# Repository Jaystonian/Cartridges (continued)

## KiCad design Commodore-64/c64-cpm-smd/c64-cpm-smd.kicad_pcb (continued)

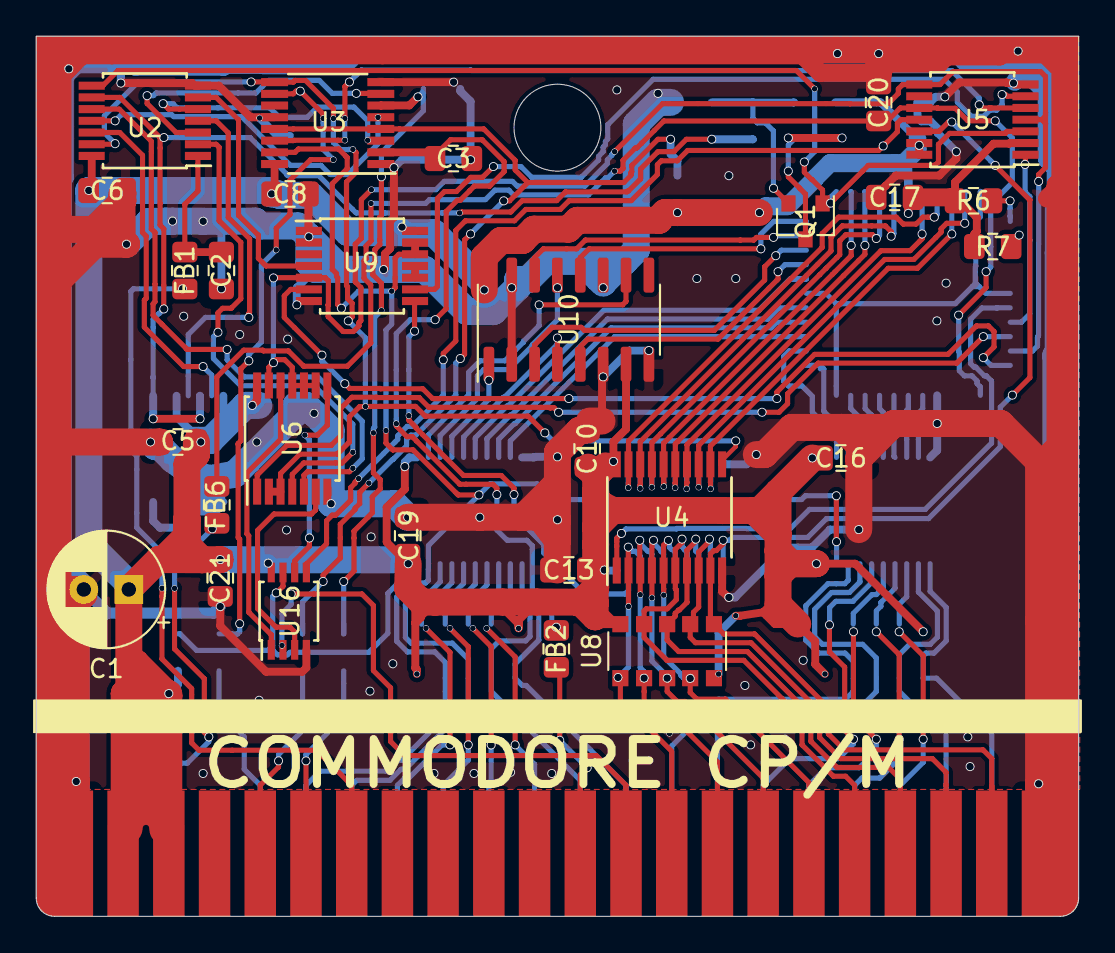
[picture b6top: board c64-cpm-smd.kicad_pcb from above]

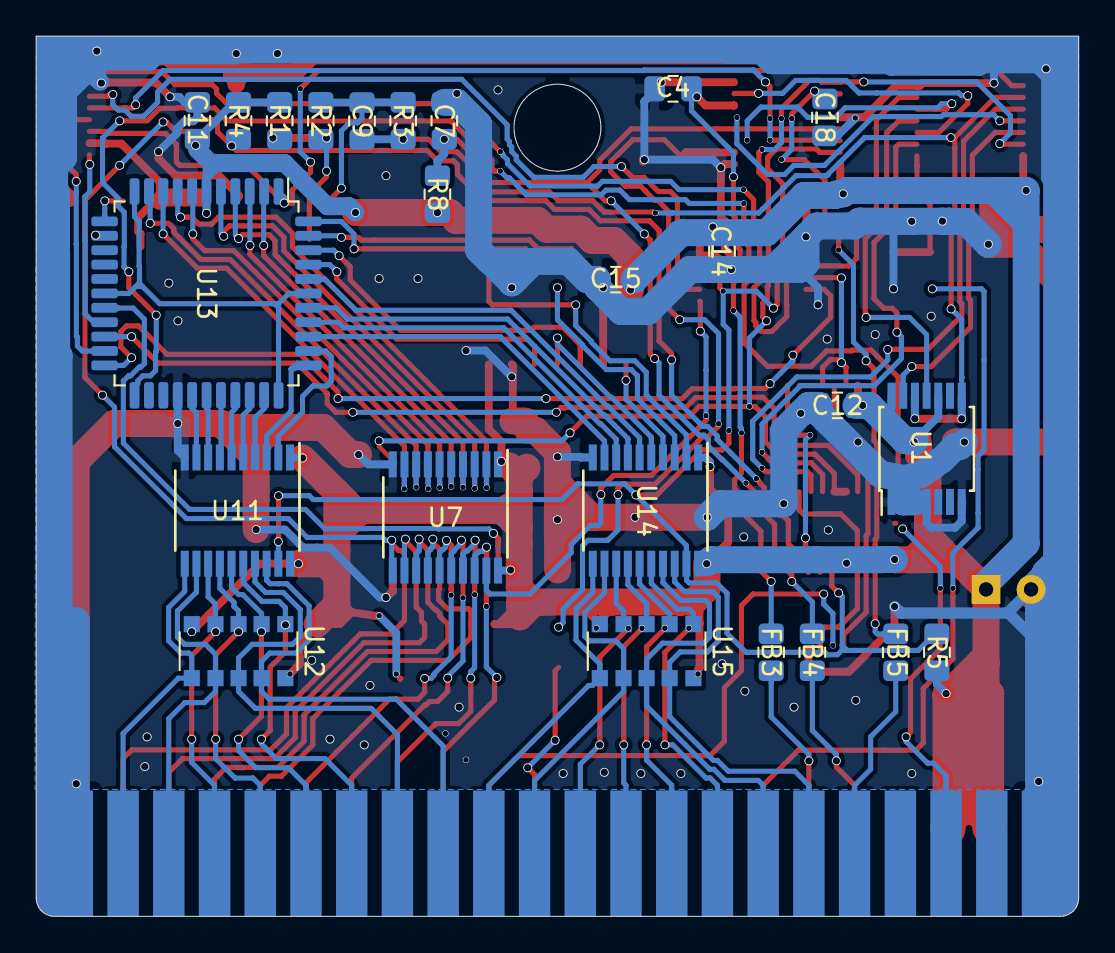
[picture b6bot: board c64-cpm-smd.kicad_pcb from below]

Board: 2 copper layers, 57.9 x 48.9 mm, 53 parts (24 on the bottom side), 97 nets.

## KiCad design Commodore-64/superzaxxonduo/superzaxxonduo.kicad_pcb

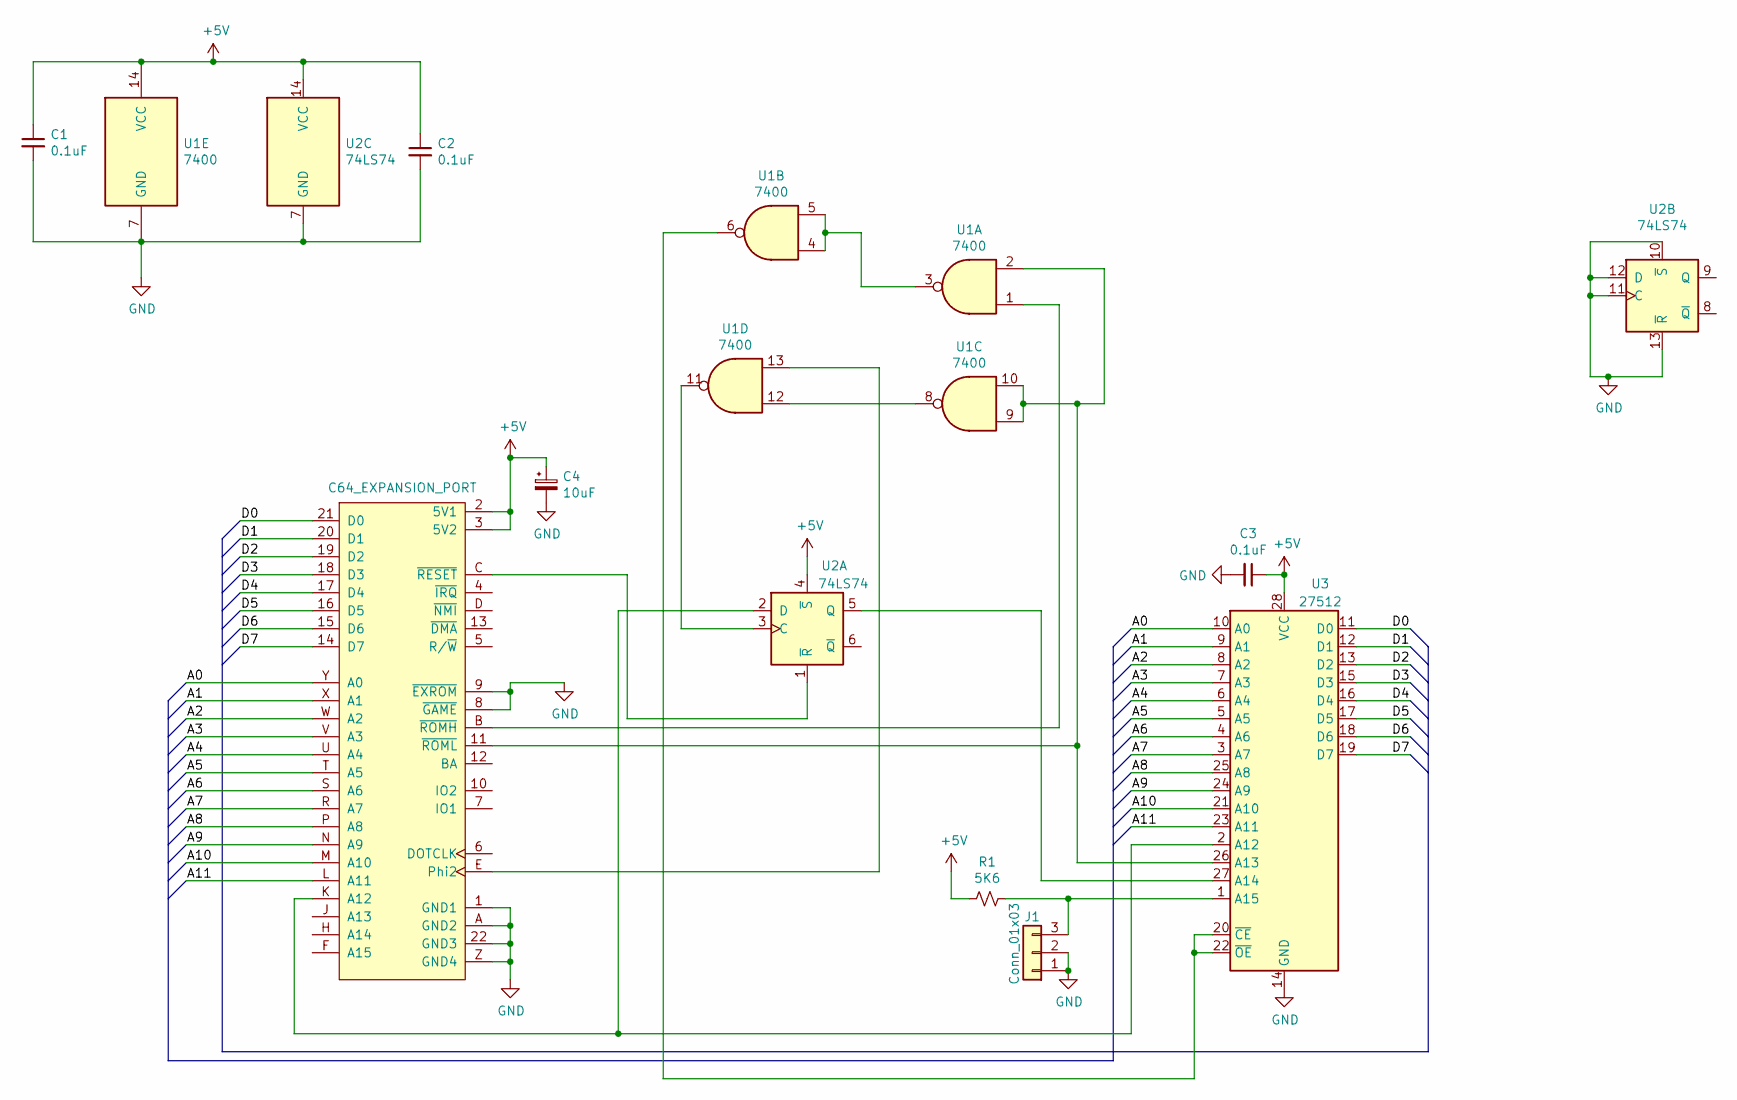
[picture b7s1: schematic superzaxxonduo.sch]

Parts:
C1, C2, C3: 0.1uF; C_Disc_D3.0mm_W1.6mm_P2.50mm
C4: 10uF; CP_Radial_D5.0mm_P2.50mm
J1: Conn_01x03; PinSocket_1x03_P2.54mm_Horizontal
R1: 5K6; R_Axial_DIN0204_L3.6mm_D1.6mm_P5.08mm_Horizontal
U1: 7400; DIP-14_W7.62mm
U2: 74LS74; DIP-14_W7.62mm
U3: 27512; DIP-28_W15.24mm
X1: C64_EXPANSION_PORT; C64_EXPANSION_CARD_49mm

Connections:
+5V: C1.1, C2.1, C3.1, C4.1, R1.1, U1.14 (VCC), U2.4 (~S), U2.14 (VCC), U3.28 (VCC), X1.2 (5V1), X1.3 (5V2); also elsewhere on the board
/A0: U3.10 (A0), X1.Y (A0); also elsewhere on the board
/A1: U3.9 (A1), X1.X (A1); also elsewhere on the board
/A2: U3.8 (A2), X1.W (A2); also elsewhere on the board
/A3: U3.7 (A3), X1.V (A3); also elsewhere on the board
/A4: U3.6 (A4), X1.U (A4); also elsewhere on the board
/A5: U3.5 (A5), X1.T (A5); also elsewhere on the board
/A6: U3.4 (A6), X1.S (A6); also elsewhere on the board
/A7: U3.3 (A7), X1.R (A7); also elsewhere on the board
/A8: U3.25 (A8), X1.P (A8); also elsewhere on the board
/A9: U3.24 (A9), X1.N (A9); also elsewhere on the board
/A10: U3.21 (A10), X1.M (A10); also elsewhere on the board
/A11: U3.23 (A11), X1.L (A11); also elsewhere on the board
/D0: U3.11 (D0), X1.21 (D0); also elsewhere on the board
/D1: U3.12 (D1), X1.20 (D1); also elsewhere on the board
/D2: U3.13 (D2), X1.19 (D2); also elsewhere on the board
/D3: U3.15 (D3), X1.18 (D3); also elsewhere on the board
/D4: U3.16 (D4), X1.17 (D4); also elsewhere on the board
/D5: U3.17 (D5), X1.16 (D5); also elsewhere on the board
/D6: U3.18 (D6), X1.15 (D6); also elsewhere on the board
/D7: U3.19 (D7), X1.14 (D7); also elsewhere on the board
GND: C1.2, C2.2, C3.2, C4.2, J1.1, J1.2, U1.7 (GND), U2.7 (GND), U2.10 (~S), U2.11 (C), U2.12 (D), U2.13 (~R), U3.14 (GND), X1.1 (GND1), X1.8 (~GAME~), X1.9 (~EXROM~), X1.22 (GND3), X1.A (GND2), X1.Z (GND4); also elsewhere on the board
unnamed: J1.3, R1.2, U3.1 (A15)
unnamed 23: U1.1, X1.B (~ROMH~); also elsewhere on the board
unnamed: U1.3, U1.4, U1.5
unnamed: U1.6, U3.20 (~CE), U3.22 (~OE)
unnamed 26: U1.2, U1.9, U1.10, U3.26 (A13), X1.11 (~ROML~); also elsewhere on the board
unnamed: U1.11, U2.3 (C)
unnamed: U1.8, U1.12
unnamed 29: U1.13, X1.E (Phi2); also elsewhere on the board
unnamed 30: U2.1 (~R), X1.C (~RESET~); also elsewhere on the board
unnamed 31: U2.2 (D), U3.2 (A12), X1.K (A12); also elsewhere on the board
unnamed: U2.5 (Q), U3.27 (A14)

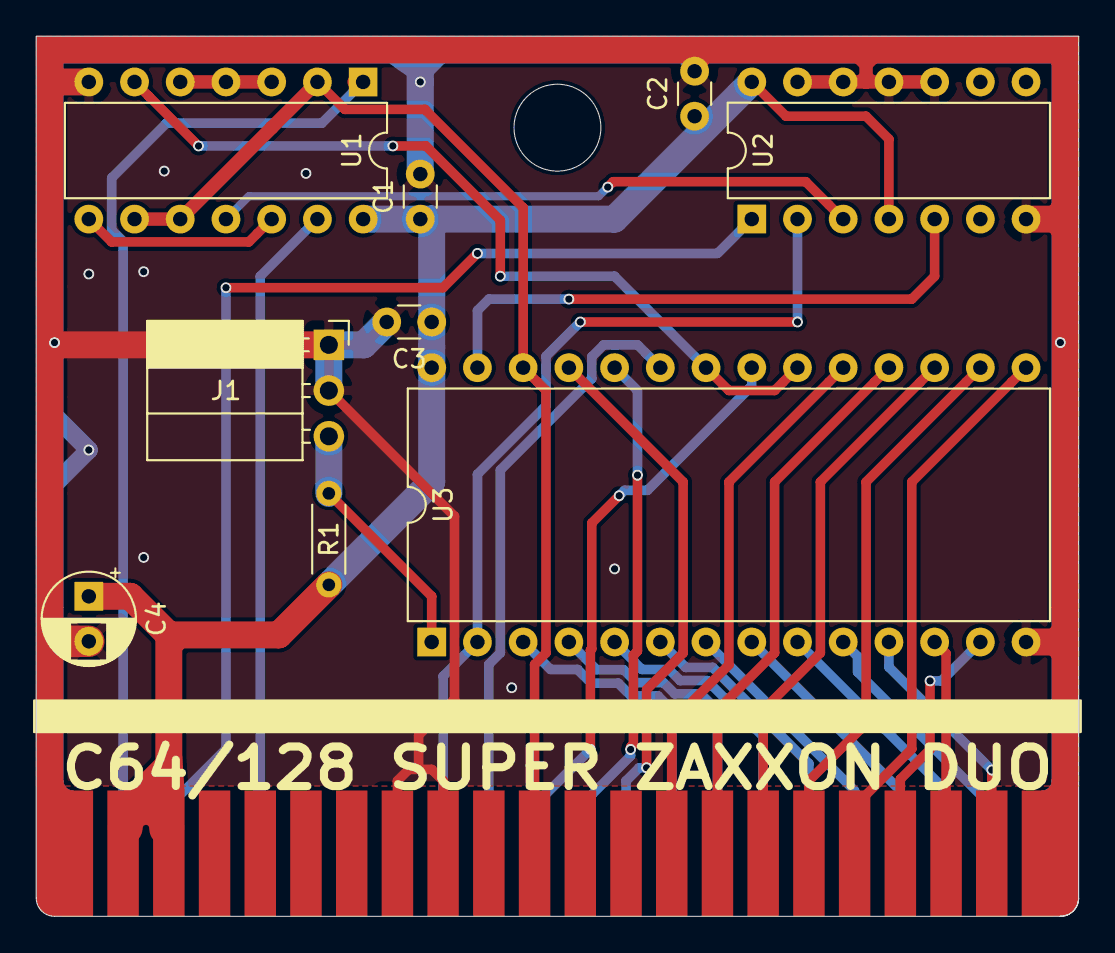
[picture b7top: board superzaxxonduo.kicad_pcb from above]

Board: 2 copper layers, 57.9 x 48.9 mm, 10 parts (0 on the bottom side), 33 nets.

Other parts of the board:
C64/128 SUPER ZAXXON DUO: C64/128 SUPER ZAXXON DUO; C64_EXPANSION_CARD_49mm

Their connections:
+5V: C64/128 SUPER ZAXXON DUO.2, C64/128 SUPER ZAXXON DUO.3; also elsewhere on the board
/A0: C64/128 SUPER ZAXXON DUO.Y; also elsewhere on the board
/A1: C64/128 SUPER ZAXXON DUO.X; also elsewhere on the board
/A2: C64/128 SUPER ZAXXON DUO.W; also elsewhere on the board
/A3: C64/128 SUPER ZAXXON DUO.V; also elsewhere on the board
/A4: C64/128 SUPER ZAXXON DUO.U; also elsewhere on the board
/A5: C64/128 SUPER ZAXXON DUO.T; also elsewhere on the board
/A6: C64/128 SUPER ZAXXON DUO.S; also elsewhere on the board
/A7: C64/128 SUPER ZAXXON DUO.R; also elsewhere on the board
/A8: C64/128 SUPER ZAXXON DUO.P; also elsewhere on the board
/A9: C64/128 SUPER ZAXXON DUO.N; also elsewhere on the board
/A10: C64/128 SUPER ZAXXON DUO.M; also elsewhere on the board
/A11: C64/128 SUPER ZAXXON DUO.L; also elsewhere on the board
/D0: C64/128 SUPER ZAXXON DUO.21; also elsewhere on the board
/D1: C64/128 SUPER ZAXXON DUO.20; also elsewhere on the board
/D2: C64/128 SUPER ZAXXON DUO.19; also elsewhere on the board
/D3: C64/128 SUPER ZAXXON DUO.18; also elsewhere on the board
/D4: C64/128 SUPER ZAXXON DUO.17; also elsewhere on the board
/D5: C64/128 SUPER ZAXXON DUO.16; also elsewhere on the board
/D6: C64/128 SUPER ZAXXON DUO.15; also elsewhere on the board
/D7: C64/128 SUPER ZAXXON DUO.14; also elsewhere on the board
GND: C64/128 SUPER ZAXXON DUO.1, C64/128 SUPER ZAXXON DUO.8, C64/128 SUPER ZAXXON DUO.9, C64/128 SUPER ZAXXON DUO.22, C64/128 SUPER ZAXXON DUO.A, C64/128 SUPER ZAXXON DUO.Z; also elsewhere on the board
unnamed 23: C64/128 SUPER ZAXXON DUO.B; also elsewhere on the board
unnamed 26: C64/128 SUPER ZAXXON DUO.11; also elsewhere on the board
unnamed 29: C64/128 SUPER ZAXXON DUO.E; also elsewhere on the board
unnamed 30: C64/128 SUPER ZAXXON DUO.C; also elsewhere on the board
unnamed 31: C64/128 SUPER ZAXXON DUO.K; also elsewhere on the board

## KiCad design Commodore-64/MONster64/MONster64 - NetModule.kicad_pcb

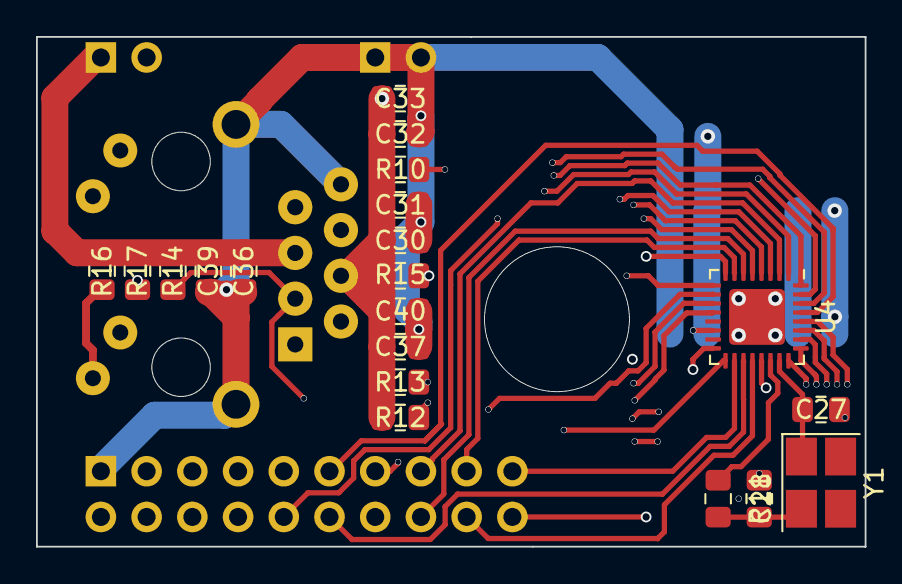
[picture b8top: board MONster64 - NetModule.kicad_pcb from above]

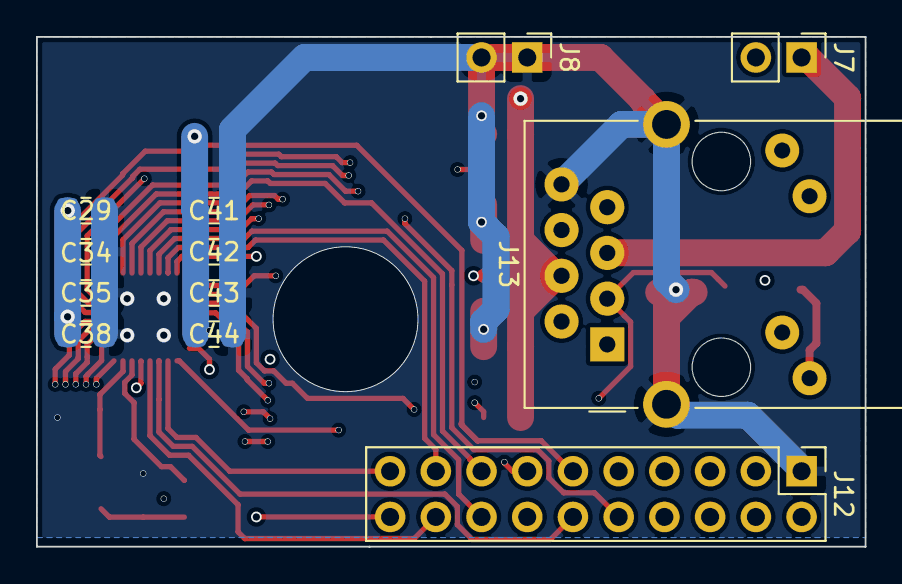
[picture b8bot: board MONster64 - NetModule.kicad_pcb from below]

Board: 6 copper layers, 46.0 x 28.3 mm, 32 parts (12 on the bottom side), 33 nets.

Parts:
C27, C28: 18p; C_0805_2012Metric_Pad1.15x1.40mm_HandSolder
C29, C41: 10u; C_0805_2012Metric_Pad1.15x1.40mm_HandSolder
C30, C32, C34, C39, C40, C42: 1u; C_0805_2012Metric_Pad1.15x1.40mm_HandSolder
C31, C33, C35, C36, C37, C43: 100n; C_0805_2012Metric_Pad1.15x1.40mm_HandSolder
C38, C44: 10n; C_0805_2012Metric_Pad1.15x1.40mm_HandSolder
J7: 3v3; PinHeader_1x02_P2.54mm_Vertical
J8: GND; PinHeader_1x02_P2.54mm_Vertical
J12: Conn_01x20; PinHeader_2x10_P2.54mm_Vertical
J13: RJ45_Amphenol_RJMG1BD3B8K1ANR
R10: 4k87; R_0805_2012Metric_Pad1.15x1.40mm_HandSolder
R11: 22R; R_0805_2012Metric_Pad1.15x1.40mm_HandSolder
R12, R13, R14, R15: 49r9; R_0805_2012Metric_Pad1.15x1.40mm_HandSolder
R16, R17: 510R; R_0805_2012Metric_Pad1.15x1.40mm_HandSolder
U4: DP83822IFRHB; VQFN-32-1EP_5x5mm_P0.5mm_EP3.1x3.1mm
Y1: Crystal; Crystal_SMD_SeikoEpson_TSX3225-4Pin_3.2x2.5mm_HandSoldering

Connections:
+3V3: C29.1, C30.1, C31.1, C32.1, C33.1, C34.1, C35.1, C36.1, C37.1, C38.1, C39.1, C40.1, C41.1, C42.1, C43.1, C44.1, J7.1, J7.2, J13.R4, J13.R5, R10.2, R12.1, R13.2, R14.1, R15.2, R16.1, R17.1, U4.14, U4.21
/ETH_COL: J12.11, U4.29
/ETH_CRS: J12.14, U4.27
/ETH_MDC: J12.18, U4.20
/ETH_MDIO: J12.12, U4.19
/ETH_RX_CLK: J12.13, U4.25
/ETH_RX_D0: J12.7, U4.30
/ETH_RX_D1: J12.6, U4.31
/ETH_RX_D2: J12.5, U4.32
/ETH_RX_D3: J12.3, U4.1
/ETH_RX_DV: J12.8, U4.26
/ETH_RX_ER: J12.4, U4.28
/ETH_TX_CLK: J12.15, U4.2
/ETH_TX_D0: J12.9, U4.4
/ETH_TX_D1: J12.10, U4.5
/ETH_TX_D2: J12.16, U4.6
/ETH_TX_D3: J12.17, U4.7
/ETH_TX_EN: J12.2, U4.3
/ETH_XI: C27.1, U4.23, Y1.1
/ETH_XO: R11.1, U4.22
/ETH_~INTPD: J12.20, U4.8
/~RST: J12.19, U4.18
GND: C27.2, C28.2, C29.2, C30.2, C31.2, C32.2, C33.2, C34.2, C35.2, C36.2, C37.2, C38.2, C39.2, C40.2, C41.2, C42.2, C43.2, C44.2, J8.1, J8.2, J12.1, J13.13, J13.R8, U4.33
unnamed: C28.1, R11.2, Y1.2
unnamed: J13.L1, R17.2
unnamed: J13.L2, U4.17
unnamed: J13.L3, U4.24
unnamed: J13.L4, R16.2
unnamed: J13.R1, R12.2, U4.12
unnamed: J13.R2, R13.1, U4.11
unnamed: J13.R3, R14.2, U4.10
unnamed: J13.R6, R15.1, U4.9
unnamed: R10.1, U4.16

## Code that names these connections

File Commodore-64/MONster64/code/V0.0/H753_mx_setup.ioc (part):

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Mcu.Name=STM32H753VITx
Mcu.Package=LQFP100
Mcu.UserName=STM32H753VITx
PA10.GPIOParameters=GPIO_Label
PA10.GPIO_Label=PIN_DMA
PA10.Signal=GPIO_Input
PA11.Mode=Device_Only
PA11.Signal=USB_OTG_FS_DM
PA12.Mode=Device_Only
PA12.Signal=USB_OTG_FS_DP
PA13\ (JTMS/SWDIO).Signal=DEBUG_JTMS-SWDIO
PA14\ (JTCK/SWCLK).Signal=DEBUG_JTCK-SWCLK
PA15\ (JTDI).GPIOParameters=GPIO_Label
PA15\ (JTDI).GPIO_Label=PIN_A7
PA15\ (JTDI).Signal=GPIO_Input
PA4.Signal=GPXTI4
PA5.Signal=GPXTI5
PA8.GPIOParameters=GPIO_Label
PA8.GPIO_Label=PIN_ROML
PA8.Signal=GPIO_Input
PA9.GPIOParameters=GPIO_Label
PA9.GPIO_Label=PIN_BA
PA9.Signal=GPIO_Input
PB14.Mode=SD_4_bits_Wide_bus
PB14.Signal=SDMMC2_D0
PB15.Mode=SD_4_bits_Wide_bus
PB15.Signal=SDMMC2_D1
PB2.Mode=Single Bank 2
PB2.Signal=QUADSPI_CLK
PB3\ (JTDO/TRACESWO).Mode=SD_4_bits_Wide_bus
PB3\ (JTDO/TRACESWO).Signal=SDMMC2_D2
PB4\ (NJTRST).Mode=SD_4_bits_Wide_bus
PB4\ (NJTRST).Signal=SDMMC2_D3
PB5.GPIOParameters=GPIO_Label
PB5.GPIO_Label=PIN_D6
PB5.Signal=GPIO_Input
PB6.GPIOParameters=GPIO_Label
PB6.GPIO_Label=PIN_D5
PB6.Signal=GPIO_Input
PB7.GPIOParameters=GPIO_Label
PB7.GPIO_Label=PIN_D4
PB7.Signal=GPIO_Input
PB8.GPIOParameters=GPIO_Label
PB8.GPIO_Label=PIN_D3
PB8.Signal=GPIO_Input
PB9.GPIOParameters=GPIO_Label
PB9.GPIO_Label=PIN_D2
PB9.Signal=GPIO_Input
PC10.GPIOParameters=GPIO_Label
PC10.GPIO_Label=PIN_A6
PC10.Signal=GPIO_Input
PC11.Mode=Single Bank 2
PC11.Signal=QUADSPI_BK2_NCS
PC12.GPIOParameters=GPIO_Label
PC12.GPIO_Label=PIN_A5
PC12.Signal=GPIO_Input
PC13.GPIOParameters=GPIO_Label
PC13.GPIO_Label=PIN_XP1
PC13.Signal=GPIO_Input
PC14-OSC32_IN\ (OSC32_IN).GPIOParameters=GPIO_Label
PC14-OSC32_IN\ (OSC32_IN).GPIO_Label=PIN_XP2
PC14-OSC32_IN\ (OSC32_IN).Signal=GPIO_Input
PC15-OSC32_OUT\ (OSC32_OUT).GPIOParameters=GPIO_Label
PC15-OSC32_OUT\ (OSC32_OUT).GPIO_Label=PIN_XP3
PC15-OSC32_OUT\ (OSC32_OUT).Signal=GPIO_Input
PC6.GPIOParameters=GPIO_Label
PC6.GPIO_Label=PIN_IO1
PC6.Signal=GPIO_Input
PC7.GPIOParameters=GPIO_Label
PC7.GPIO_Label=PIN_GAME
PC7.Signal=GPIO_Input
PC8.GPIOParameters=GPIO_Label
PC8.GPIO_Label=PIN_EXROM
PC8.Signal=GPIO_Input
PC9.GPIOParameters=GPIO_Label
PC9.GPIO_Label=PIN_IO2
PC9.Signal=GPIO_Input
PD0.GPIOParameters=GPIO_Label
PD0.GPIO_Label=PIN_A4
PD0.Signal=GPIO_Input
PD1.GPIOParameters=GPIO_Label
PD1.GPIO_Label=PIN_A3
PD1.Signal=GPIO_Input
PD10.GPIOParameters=GPIO_Label
PD10.GPIO_Label=PIN_A11
PD10.Signal=GPIO_Input
PD11.GPIOParameters=GPIO_Label
PD11.GPIO_Label=PIN_A10
PD11.Signal=GPIO_Input
PD12.GPIOParameters=GPIO_Label
PD12.GPIO_Label=PIN_A9
PD12.Signal=GPIO_Input
PD13.GPIOParameters=GPIO_Label
PD13.GPIO_Label=PIN_A8
PD13.Signal=GPIO_Input
PD14.GPIOParameters=GPIO_Label
PD14.GPIO_Label=PIN_IRQ
PD14.Signal=GPIO_Input
PD15.GPIOParameters=GPIO_Label
PD15.GPIO_Label=PIN_RW
PD15.Signal=GPIO_Input
PD2.GPIOParameters=GPIO_Label
PD2.GPIO_Label=PIN_A2
PD2.Signal=GPIO_Input
PD3.GPIOParameters=GPIO_Label
PD3.GPIO_Label=PIN_A1
PD3.Signal=GPIO_Input
PD4.GPIOParameters=GPIO_Label
PD4.GPIO_Label=PIN_A0
PD4.Signal=GPIO_Input
PD5.GPIOParameters=GPIO_Label
PD5.GPIO_Label=PIN_D7
PD5.Signal=GPIO_Input
PD6.Mode=SD_4_bits_Wide_bus
PD6.Signal=SDMMC2_CK
PD7.Mode=SD_4_bits_Wide_bus
PD7.Signal=SDMMC2_CMD
PD8.GPIOParameters=GPIO_Label
PD8.GPIO_Label=PIN_A13
PD8.Signal=GPIO_Input
PD9.GPIOParameters=GPIO_Label
PD9.GPIO_Label=PIN_A12
PD9.Signal=GPIO_Input
PE0.GPIOParameters=GPIO_Label
PE0.GPIO_Label=PIN_D1
PE0.Signal=GPIO_Input
PE1.GPIOParameters=GPIO_Label
PE1.GPIO_Label=PIN_D0
PE1.Signal=GPIO_Input
PE10.Mode=Single Bank 2
PE10.Signal=QUADSPI_BK2_IO3
PE11.GPIOParameters=GPIO_Label
PE11.GPIO_Label=PIN_A14
PE11.Signal=GPIO_Input
PE12.GPIOParameters=GPIO_Label
PE12.GPIO_Label=PIN_A15
PE12.Signal=GPIO_Input
PE13.GPIOParameters=GPIO_Label
PE13.GPIO_Label=PIN_PHI2
PE13.Signal=GPIO_Input
PE14.GPIOParameters=GPIO_Label
PE14.GPIO_Label=PIN_NMI
PE14.Signal=GPIO_Input
PE15.GPIOParameters=GPIO_Label
PE15.GPIO_Label=PIN_ROMH
PE15.Signal=GPIO_Input
PE3.GPIOParameters=GPIO_Label
PE3.GPIO_Label=SD_DET1
PE3.Signal=GPIO_Input
PE4.GPIOParameters=GPIO_Label
PE4.GPIO_Label=SD_DET2
PE4.Signal=GPIO_Input
PE5.GPIOParameters=GPIO_Label
PE5.GPIO_Label=PIN_RST_O
PE5.Signal=GPIO_Output
PE6.GPIOParameters=GPIO_Label
PE6.GPIO_Label=PIN_LED
PE6.Signal=GPIO_Output
PE7.Mode=Single Bank 2
PE7.Signal=QUADSPI_BK2_IO0
PE8.Mode=Single Bank 2
PE8.Signal=QUADSPI_BK2_IO1
PE9.Mode=Single Bank 2
PE9.Signal=QUADSPI_BK2_IO2
PH0-OSC_IN\ (PH0).Mode=HSE-External-Clock-Source
PH0-OSC_IN\ (PH0).Signal=RCC_OSC_IN
RCC.HSE_VALUE=8000000
RCC.SYSCLKFreq_VALUE=468000000
RCC.SYSCLKSource=RCC_SYSCLKSOURCE_PLLCLK
board=custom

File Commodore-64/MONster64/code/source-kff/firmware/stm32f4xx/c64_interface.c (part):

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 *    misrepresented as being the original software.
 * 3. This notice may not be removed or altered from any source distribution.
 */
#define MENU_RAM_SIGNATURE  "KungFu:Menu"

static inline void set_menu_signature(void)
{
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}

/*************************************************
* C64 address bus on PB0-PB15
*************************************************/
static inline volatile uint16_t c64_addr_read()
{
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}

/*************************************************
* C64 data bus on PC0-PC7
*************************************************/
static inline volatile uint8_t c64_data_read()
{
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{
    *((volatile uint8_t *)&GPIOC->ODR) = data;

    // Make PC0-PC7 outout
    *((volatile uint16_t *)&GPIOC->MODER) = 0x5555;
}

static inline void c64_data_input(void)
{
    // Make PC0-PC7 input
    *((volatile uint16_t *)&GPIOC->MODER) = 0x0000;
}

static void c64_data_config(void)
{
    // Make PC0-PC7 input
    c64_data_input();
}

/*************************************************
* C64 control bus on PA0-PA3 and PA6-PA7
* Menu button & special button on PA4 & PA5
*************************************************/
#define C64_WRITE   0x01    // R/W on PA0
#define C64_IO1     0x02    // IO1 on PA1
#define C64_IO2     0x04    // IO1 on PA2
#define C64_BA      0x08    // BA on PA3
#define MENU_BTN    0x10    // Menu button on PA4
#define SPECIAL_BTN 0x20    // Special button on PA5
#define C64_ROML    0x40    // ROML on PA6
#define C64_ROMH    0x80    // ROMH on PA7

static inline volatile uint8_t c64_control_read()
{
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
static void c64_control_config(void)
{
    // Make PA0-PA3 and PA6-PA7 input
    GPIOA->MODER &= ~(GPIO_MODER_MODER0|GPIO_MODER_MODER1|GPIO_MODER_MODER2|
                      GPIO_MODER_MODER3|GPIO_MODER_MODER6|GPIO_MODER_MODER7);
}
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}

/*************************************************
* C64 GAME and EXROM on PC14 & PC15
* Status LED on PC13
*************************************************/
#define C64_GAME_HIGH   GPIO_BSRR_BS14
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}

/*************************************************
* C64 IRQ and NMI on PA9 & PA10
*************************************************/
#define C64_IRQ_HIGH        GPIO_BSRR_BS9
#define C64_IRQ_LOW         GPIO_BSRR_BR9
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}

/*************************************************
* Menu button and special button on PA4 & PA5
*************************************************/
static inline bool menu_button(void)
{
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
static void button_config(void)
{
    // Make PA4 and PA5 input
    GPIOA->MODER &= ~(GPIO_MODER_MODER4|GPIO_MODER_MODER5);

    // Enable pull-down
    MODIFY_REG(GPIOA->PUPDR, GPIO_PUPDR_PUPD4|GPIO_PUPDR_PUPD5,
               GPIO_PUPDR_PUPD4_1|GPIO_PUPDR_PUPD5_1);

    // Enable EXTI4 interrupt on PA4
    MODIFY_REG(SYSCFG->EXTICR[1], SYSCFG_EXTICR2_EXTI4, SYSCFG_EXTICR2_EXTI4_PA);
    EXTI->IMR |= EXTI_IMR_MR4;

    // Rising edge trigger on PA4
    EXTI->RTSR |= EXTI_RTSR_TR4;
    EXTI->FTSR &= ~EXTI_FTSR_TR4;

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
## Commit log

2020-07-18 added some jumper labels to the front silkscreen
2020-07-18 added some silkscreen labels
2020-07-18 cleanup
2020-07-18 zener tweak
2020-07-27 Changed over for 1v8 operation
    - Level Translated DOTCLK for OSC_IN
    - JTAG header requires 5v instead of 3v3 to power board
    - NAND Flash memory directly connected instead of through a TXS0108
    - Dual regulator to streamline power domains.
2020-07-27 Commodore 64/128 CP/M cartridge, surface mount.
2020-07-29 Revert to 3v3
    Still need to translate DOTclk
2020-10-06 Update to fit original CP/M case better
    * Moved the left screwhole 0.5mm
    * Moved the right screwhole 1mm
    * Moved the top-right pinhole 0.2mm
    * Removed the ground traces that went between card edge pads.
2021-06-11 ZX Swin SID
    A branch and rework of https://github.com/UzixLS/zx-tsid to fit available parts.
